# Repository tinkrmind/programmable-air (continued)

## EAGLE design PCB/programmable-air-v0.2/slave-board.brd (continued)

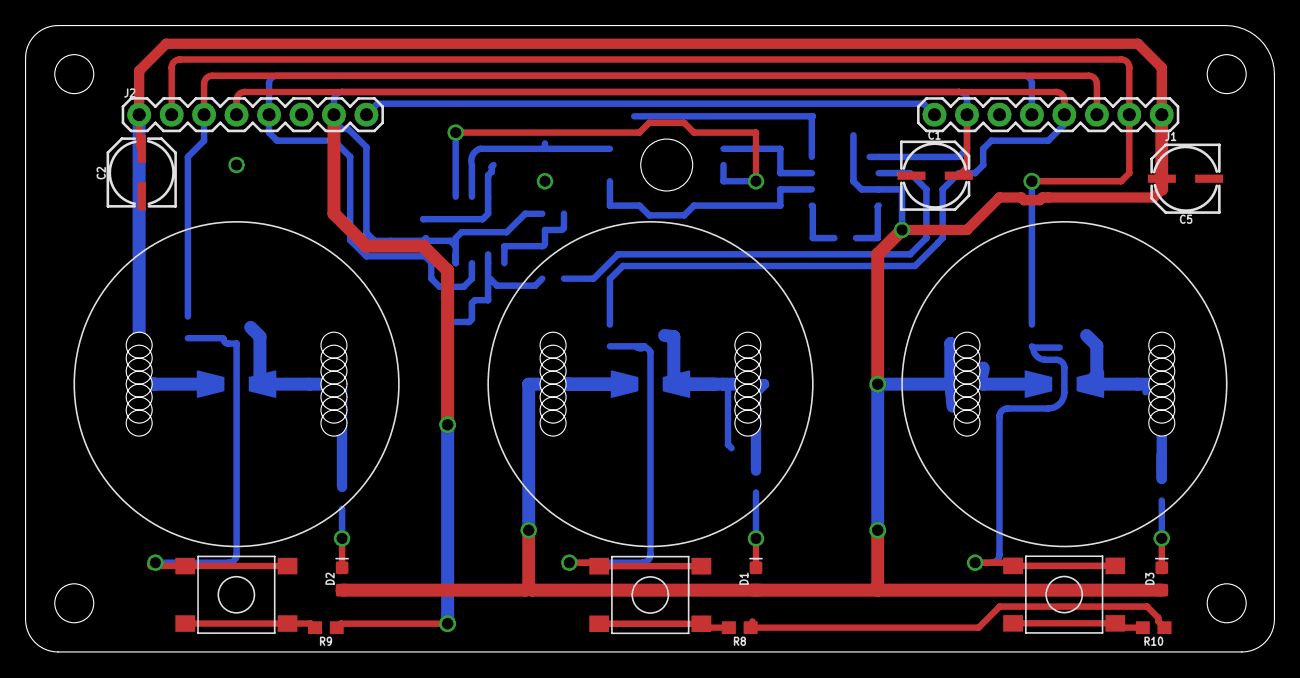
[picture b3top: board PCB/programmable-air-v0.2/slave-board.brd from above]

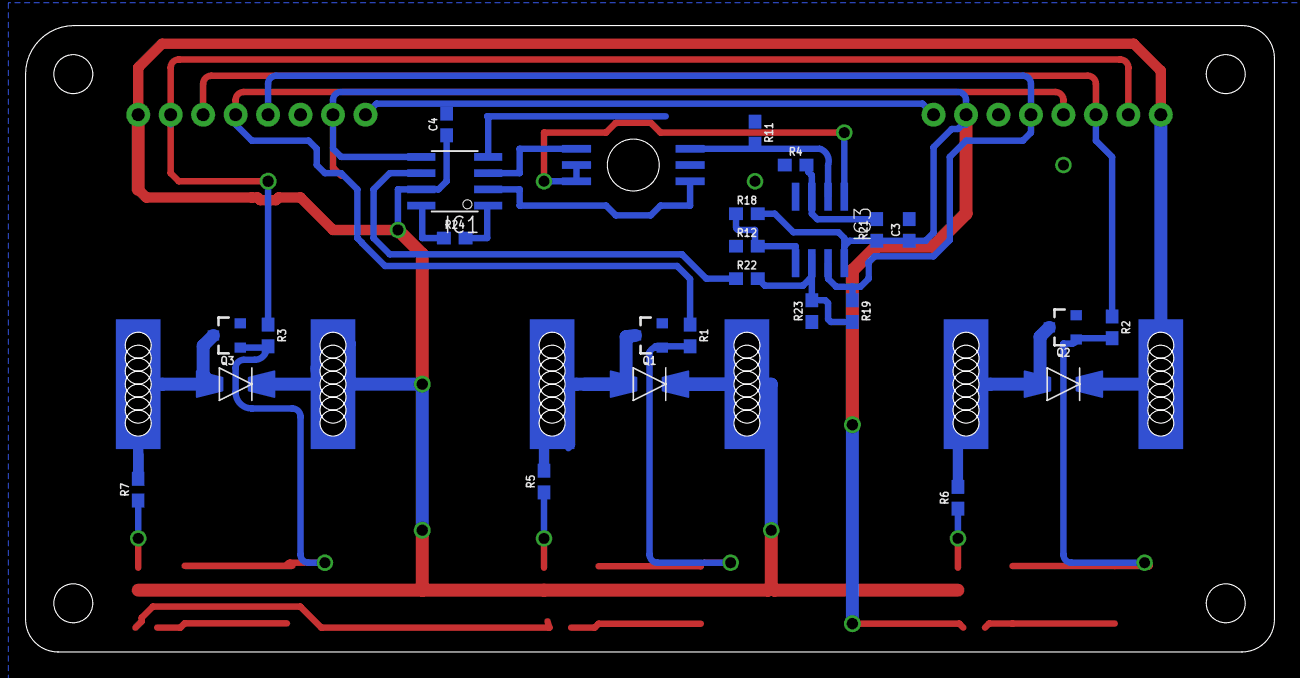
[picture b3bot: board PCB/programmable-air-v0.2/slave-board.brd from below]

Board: 2 copper layers, 97.7 x 49.0 mm, 43 parts (25 on the bottom side), 30 nets.

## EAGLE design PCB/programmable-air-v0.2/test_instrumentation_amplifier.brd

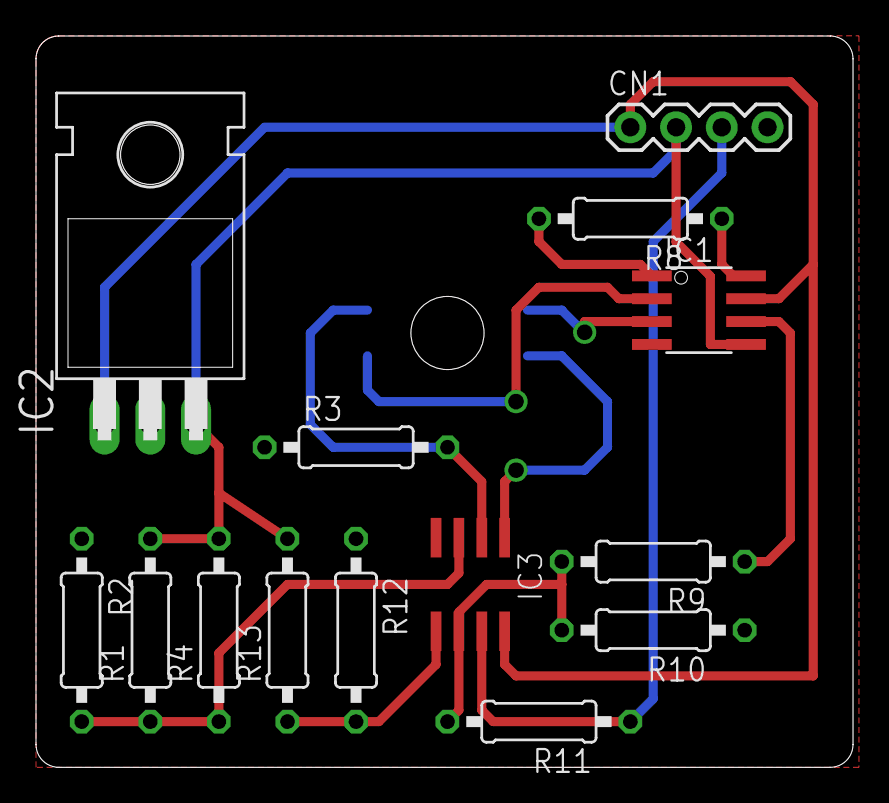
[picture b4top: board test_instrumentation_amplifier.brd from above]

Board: 2 copper layers, 45.4 x 40.6 mm, 15 parts (0 on the bottom side), 14 nets.

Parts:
CN1: 1X4-BIG; 1X04-BIG
IC1: INA126U; SO08
IC2: 7805T; TO220H
IC3: LM358MX; SO08
R1, R4: 30K; 0207/10
R2, R12, R13: 10K; 0207/10
R3: 20K; 0207/10
R8: 1.78K; 0207/10
R9, R10: 2K; 0207/10
R11: 1K; 0207/10
U$1: 2SMPP-03

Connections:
GND: CN1.4, IC1.4, IC2.2, IC3.4, R2.1, R3.1, R10.1, R12.1
unnamed: IC3.6, R9.2, R10.2, R11.2
unnamed: IC1.8, R8.1
unnamed: IC1.3, U$1.P$4
unnamed: CN1.2, IC1.5, IC2.3, R1.2, R4.2, R13.2
unnamed: IC1.1, R8.2
unnamed: IC1.2, U$1.P$1
unnamed: IC3.1, U$1.P$5, U$1.P$6
unnamed: IC1.6, R9.1
unnamed: IC3.3, R1.1, R2.2, R4.1
unnamed: IC3.5, R12.2, R13.1
unnamed: CN1.3, IC3.7, R11.1
unnamed: IC3.2, R3.2, U$1.P$3
VCC: CN1.1, IC1.7, IC2.1, IC3.8

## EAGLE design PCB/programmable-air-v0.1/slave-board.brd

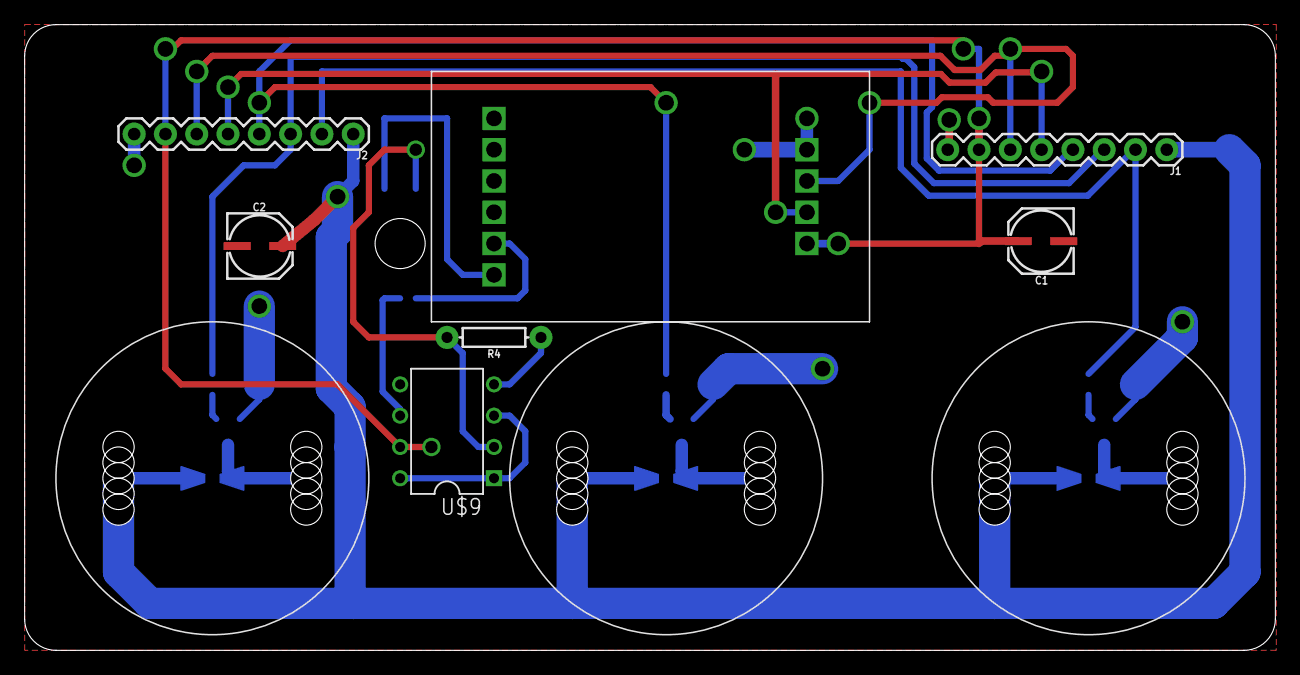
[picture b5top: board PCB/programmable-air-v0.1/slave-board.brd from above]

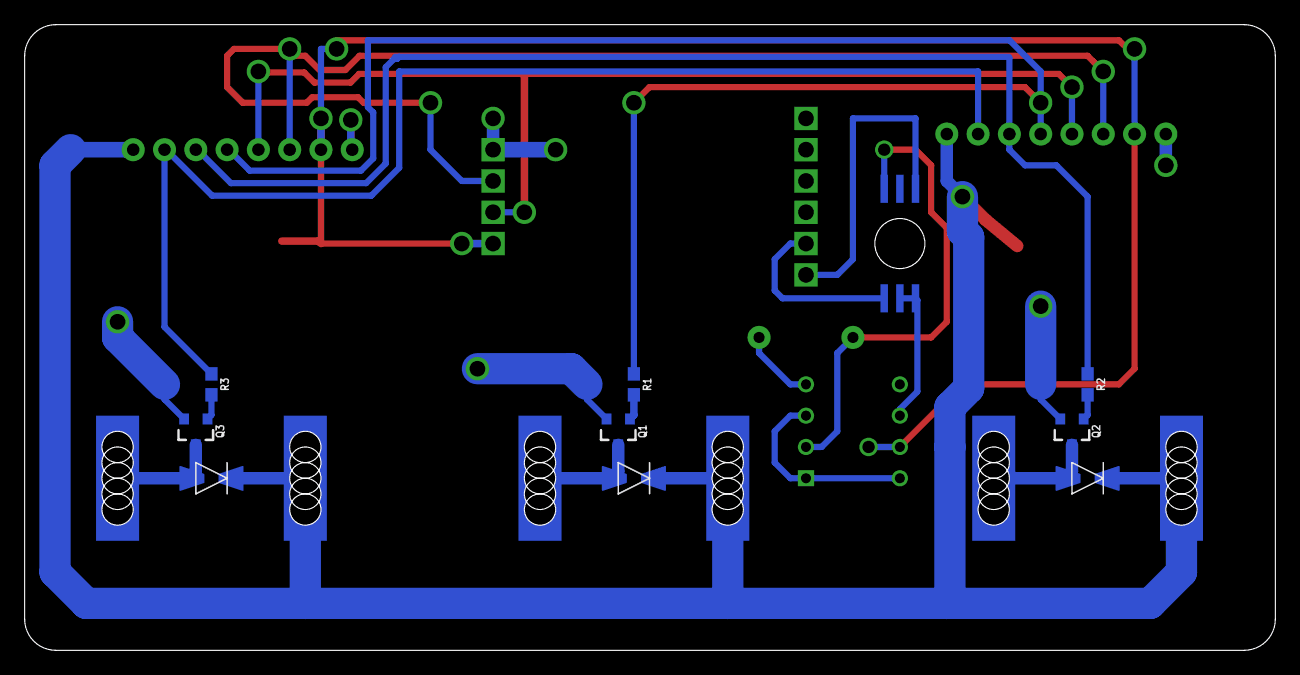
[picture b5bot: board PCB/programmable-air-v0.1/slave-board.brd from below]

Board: 2 copper layers, 101.5 x 50.8 mm, 20 parts (9 on the bottom side), 19 nets.

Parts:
C1, C2: 22uF; PANASONIC_C
J1, J2: 1X08
Q1, Q2, Q3: 600mA/40V; SOT23-3
R1, R2, R3: 1k; 0603
R4: AXIAL-0.3
U$1: HX711
U$2, U$3, U$4: CJV23-SOLENOID-VALVE; CJV23
U$5, U$6, U$7: IN4148
U$8: 2SMPP-03
U$9: LM10CN; DIP8

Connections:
GND: C1.-, C2.-, J1.8, J2.8, Q1.2, Q2.2, Q3.2, R4.P$1, U$1.P$7, U$9.4
unnamed: Q1.1, R1.2
unnamed: Q2.1, R2.2
unnamed: Q3.1, R3.2
unnamed: U$9.1, U$9.3, U$9.8
unnamed: J1.2, J2.2, R3.1
unnamed: Q3.3, U$4.P$2, U$7.P$2
unnamed: Q2.3, U$3.P$2, U$6.P$2
unnamed: Q1.3, U$2.P$2, U$5.P$2
unnamed: J1.3, J2.3, R2.1
unnamed: J1.4, J2.4, R1.1
unnamed: J1.5, J2.5, U$1.P$9
unnamed: J1.6, J2.6, U$1.P$8
unnamed: C1.+, J1.7, J2.7, U$1.P$10, U$9.7
unnamed: U$8.P$5, U$8.P$6, U$9.6
unnamed: R4.P$2, U$8.P$3, U$9.2
unnamed: U$1.P$6, U$8.P$1
unnamed: U$1.P$5, U$8.P$4
VIN: C2.+, J1.1, J2.1, U$2.P$1, U$3.P$1, U$4.P$1, U$5.P$1, U$6.P$1, U$7.P$1

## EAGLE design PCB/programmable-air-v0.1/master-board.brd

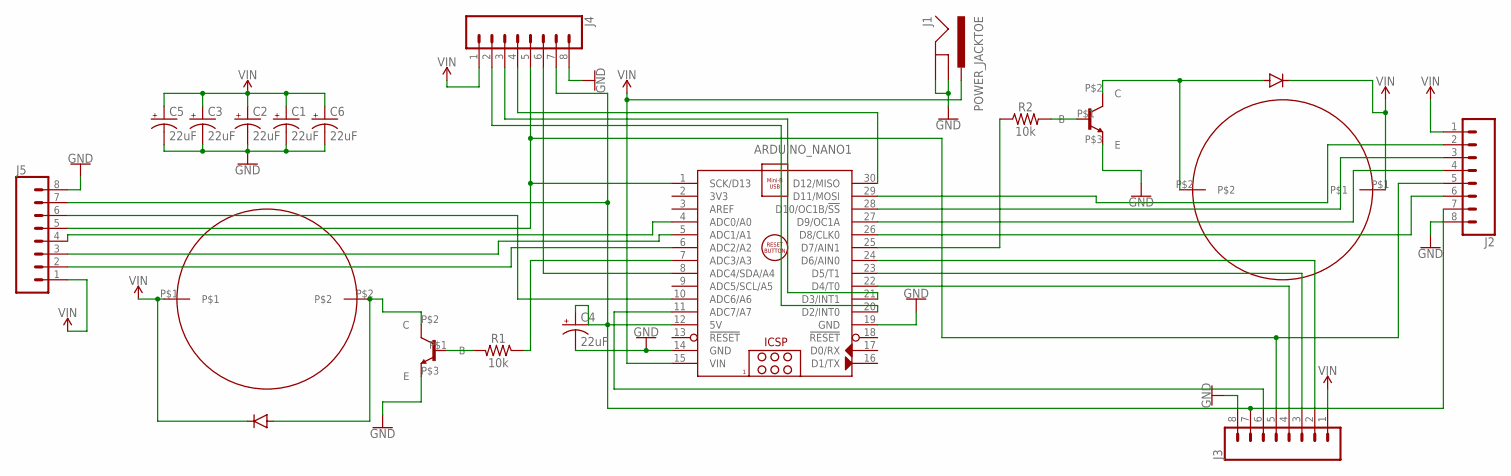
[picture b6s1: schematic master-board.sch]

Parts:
ARDUINO_NANO1: ARDUINO_NANO
C1, C2, C3, C4, C5, C6: 22uF; PANASONIC_C
J1: POWER_JACKTOE; POWER_JACK_SMD_OVERPASTE_TOE
J2, J3, J4, J5: CONN_08"; 1X08
R1, R2: 10k; 0603
U$1, U$2: AIYIMA-PUMP-A5F083; A5F083
U$3, U$4: IN4148
U$5, U$6: TIP120-TO220; TO220

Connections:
GND: ARDUINO_NANO1.14 (GND), ARDUINO_NANO1.19 (GND), C1.-, C2.-, C3.-, C4.-, C5.-, C6.-, J1.GND (GNDBREAK), J1.P$4 (GND), J2.8, J3.8, J4.8, J5.8, U$5.P$3 (E), U$6.P$3 (E)
unnamed: ARDUINO_NANO1.25 (D7/AIN1), R2.1
unnamed: R1.2, U$6.P$1 (B)
unnamed: ARDUINO_NANO1.22 (D4/T0), J3.4
unnamed: ARDUINO_NANO1.23 (D5/T1), J3.3
unnamed: U$1.P$2, U$3.P$2, U$6.P$2 (C)
unnamed: U$2.P$2, U$4.P$2, U$5.P$2 (C)
unnamed: R2.2, U$5.P$1 (B)
unnamed: ARDUINO_NANO1.21 (D3/INT1), J4.3
unnamed: ARDUINO_NANO1.24 (D6/AIN0), J3.2
unnamed: ARDUINO_NANO1.7 (ADC3/A3), R1.1
unnamed: ARDUINO_NANO1.8 (ADC4/SDA/A4), J4.6
unnamed: ARDUINO_NANO1.1 (SCK/D13), J2.5, J3.5, J4.5, J5.5
unnamed: ARDUINO_NANO1.10 (ADC6/A6), J5.6
unnamed: ARDUINO_NANO1.11 (ADC7/A7), J3.6
unnamed: ARDUINO_NANO1.20 (D2/INT0), J4.2
unnamed: ARDUINO_NANO1.30 (D12/MISO), J4.4
unnamed: ARDUINO_NANO1.12 (5V), C4.+, J2.7, J3.7, J4.7, J5.7
unnamed: ARDUINO_NANO1.26 (D8/CLK0), J2.6
unnamed: ARDUINO_NANO1.27 (D9/OC1A), J2.4
unnamed: ARDUINO_NANO1.28 (D10/OC1B/!SS), J2.3
unnamed: ARDUINO_NANO1.29 (D11/MOSI), J2.2
unnamed: ARDUINO_NANO1.6 (ADC2/A2), J5.2
unnamed: ARDUINO_NANO1.5 (ADC1/A1), J5.3
unnamed: ARDUINO_NANO1.4 (ADC0/A0), J5.4
VIN: ARDUINO_NANO1.15 (VIN), C1.+, C2.+, C3.+, C5.+, C6.+, J1.VIN0 (PWR), J2.1, J3.1, J4.1, J5.1, U$1.P$1, U$2.P$1, U$3.P$1, U$4.P$1

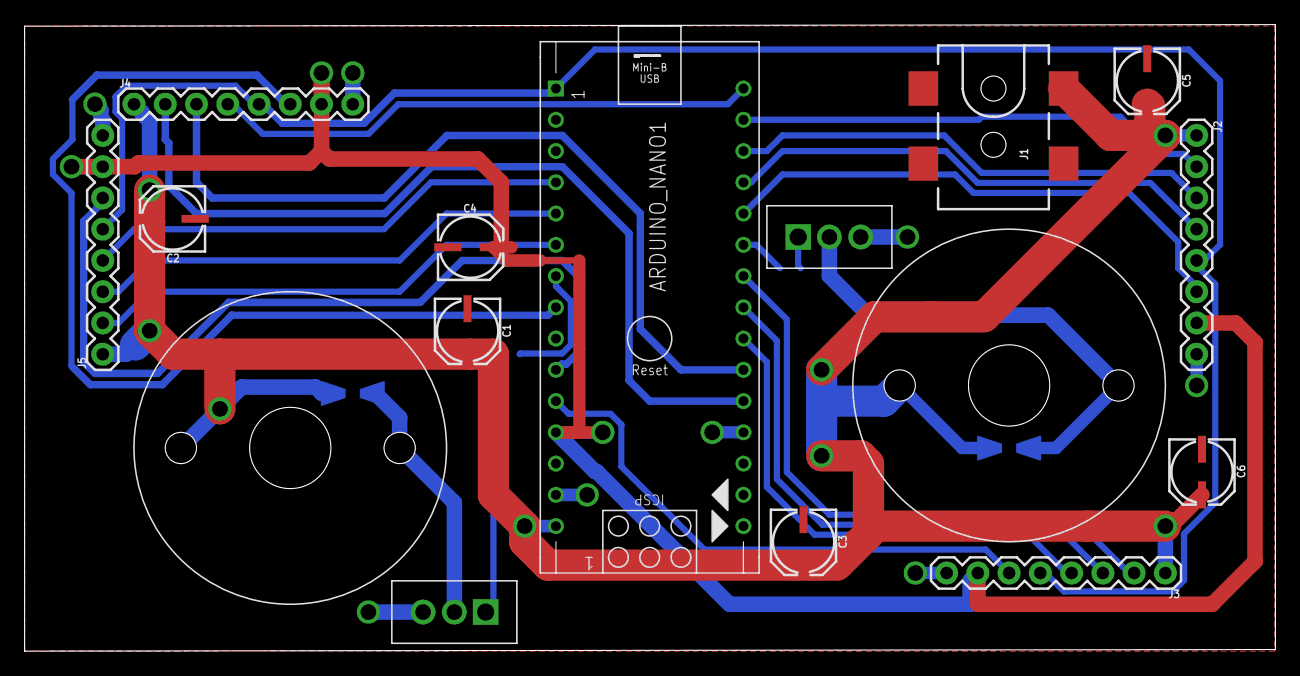
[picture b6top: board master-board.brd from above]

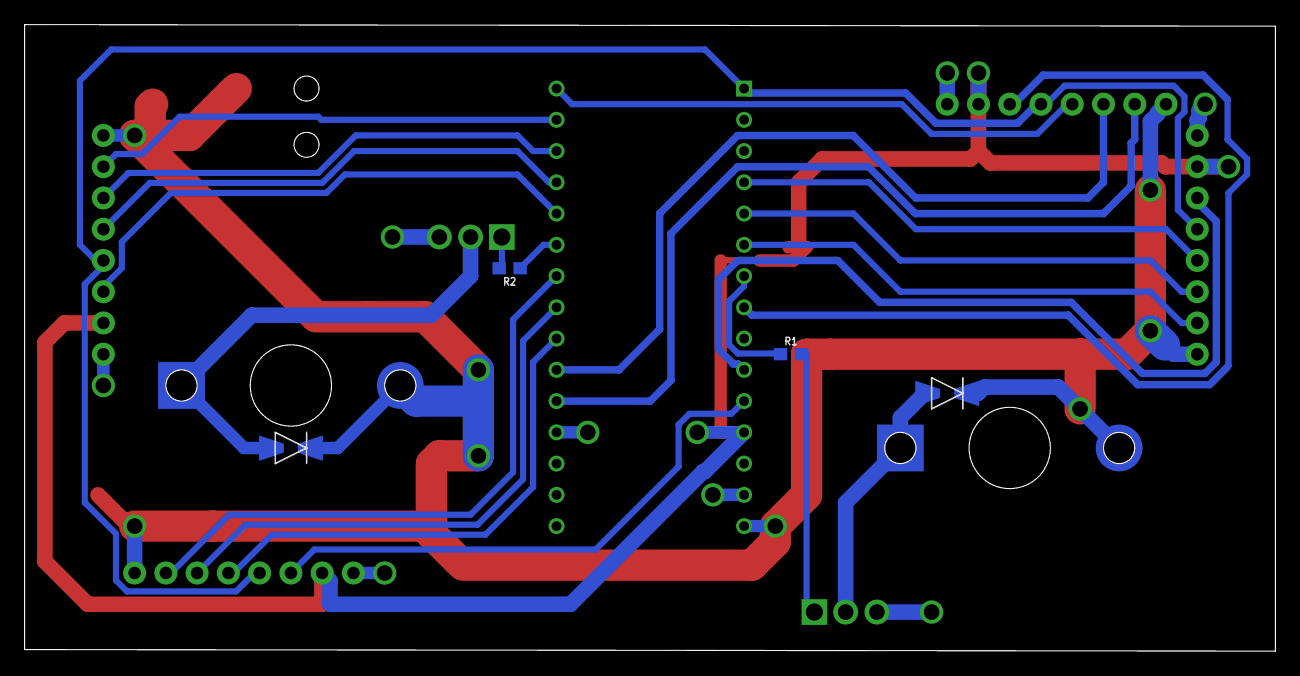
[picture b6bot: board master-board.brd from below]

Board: 2 copper layers, 101.7 x 50.9 mm, 20 parts (4 on the bottom side), 26 nets.

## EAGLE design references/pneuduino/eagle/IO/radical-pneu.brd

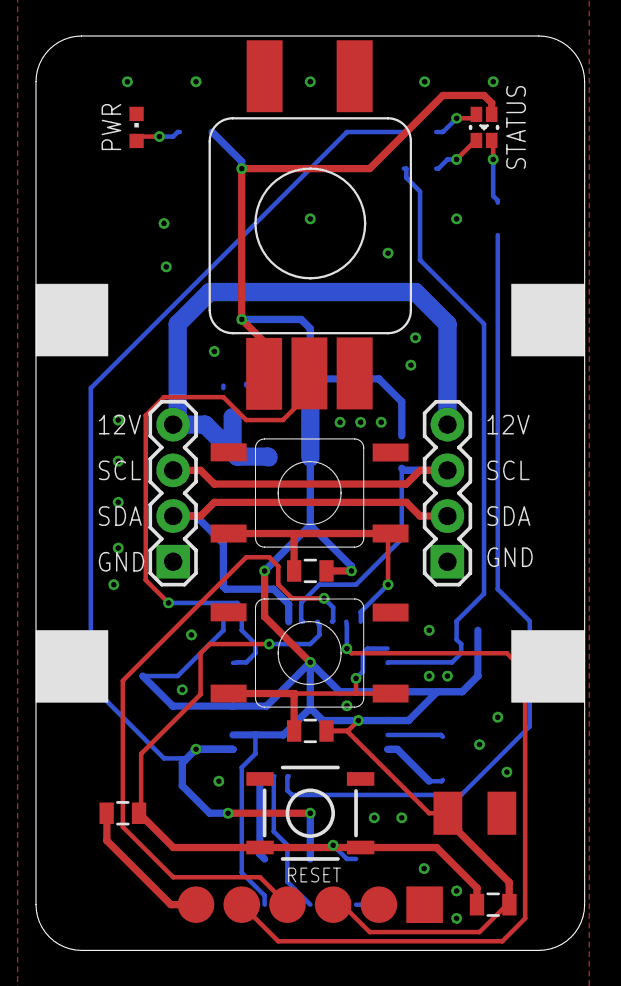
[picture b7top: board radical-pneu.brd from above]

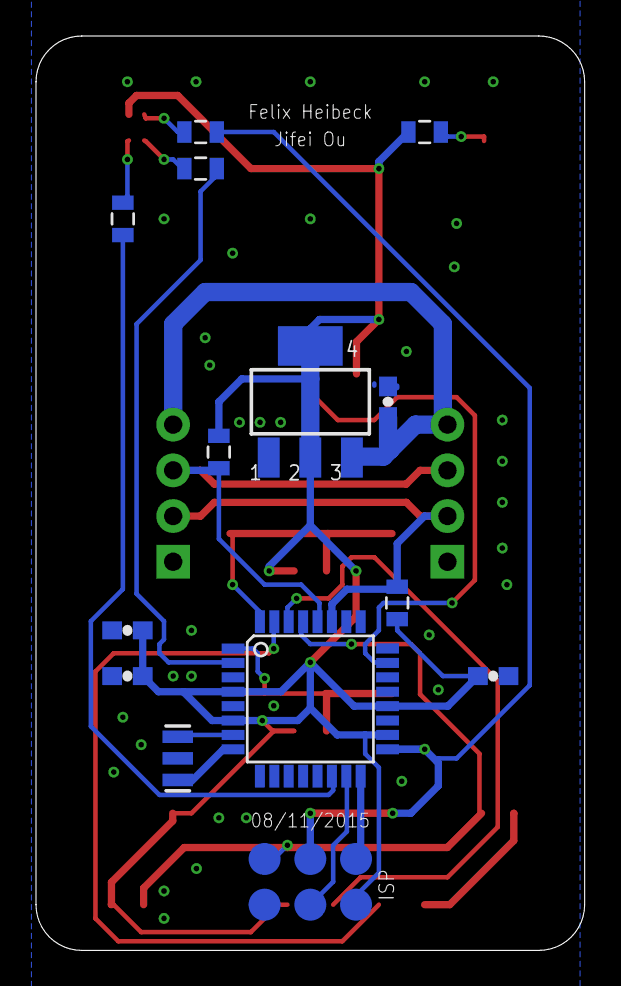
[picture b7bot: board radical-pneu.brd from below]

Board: 2 copper layers, 30.5 x 50.8 mm, 28 parts (14 on the bottom side), 23 nets.

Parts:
C1, C2, C8, C10: 0.1uF; 0603-CAP
C3: 22uF; SMC_B
C5: 0.1uF; 0805
IC3: ATMEGA328; TQFP32-08
JP2, JP3: 1X04
PWR: CHIPLED_0603
Q1: 16Mhz; RESONATOR-SMD
R1, R2, R3: 10K; 0805
R5, R6: 4.7k; 0805
R9, R11, R12, R13: 1k; 0805
S1: TAC_SWITCHSMD; TACTILE-SWITCH-SMD
U2: NCP1117-5; LINEAR_SOT223
U$1, U$3: RS-014R05; SWITCH-11MM
U$2: PRS11S
U$10: ISP_POGO; POGO_ISP
U$12: FTDI_POGO
U$21: LTST-C19FD1WT; LTST

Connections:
+5V: C2.1, C3.+, C8.1, C10.1, IC3.4, IC3.6, IC3.18, IC3.20, R1.1, R2.1, R3.1, R5.1, R6.2, R11.2, U2.2, U2.4, U$2.1, U$10.2, U$12.4, U$21.+
A0/POT: IC3.23, U$2.2
D2/BTN: IC3.32, R1.2, U$1.A, U$1.H
D3/BTN: IC3.1, R2.2, U$3.A, U$3.H
D4: IC3.2, R9.2
D10: IC3.14, R12.2
DTR: C5.2, U$12.1
GND: C1.2, C2.2, C3.-, C8.2, C10.2, IC3.3, IC3.5, IC3.21, JP2.1, JP3.1, PWR.C, Q1.2, S1.1, S1.2, U2.1, U$1.B, U$1.D, U$2.3, U$3.B, U$3.D, U$10.6, U$12.5, U$12.6
MISO: IC3.16, U$10.1
MOSI: IC3.15, U$10.4
unnamed: IC3.8, Q1.1
unnamed: IC3.7, Q1.3
unnamed: PWR.A, R11.1
unnamed: R9.1, U$21.R
unnamed: R12.1, U$21.G
unnamed: R13.1, U$21.B
RESET: C5.1, IC3.29, R3.2, S1.3, S1.4, U$10.5
RX: IC3.30, U$12.3
SCK: IC3.17, R13.2, U$10.3
SCL: IC3.28, JP2.3, JP3.3, R6.1
SDA: IC3.27, JP2.2, JP3.2, R5.2
TX: IC3.31, U$12.2
VIN: C1.1, JP2.4, JP3.4, U2.3

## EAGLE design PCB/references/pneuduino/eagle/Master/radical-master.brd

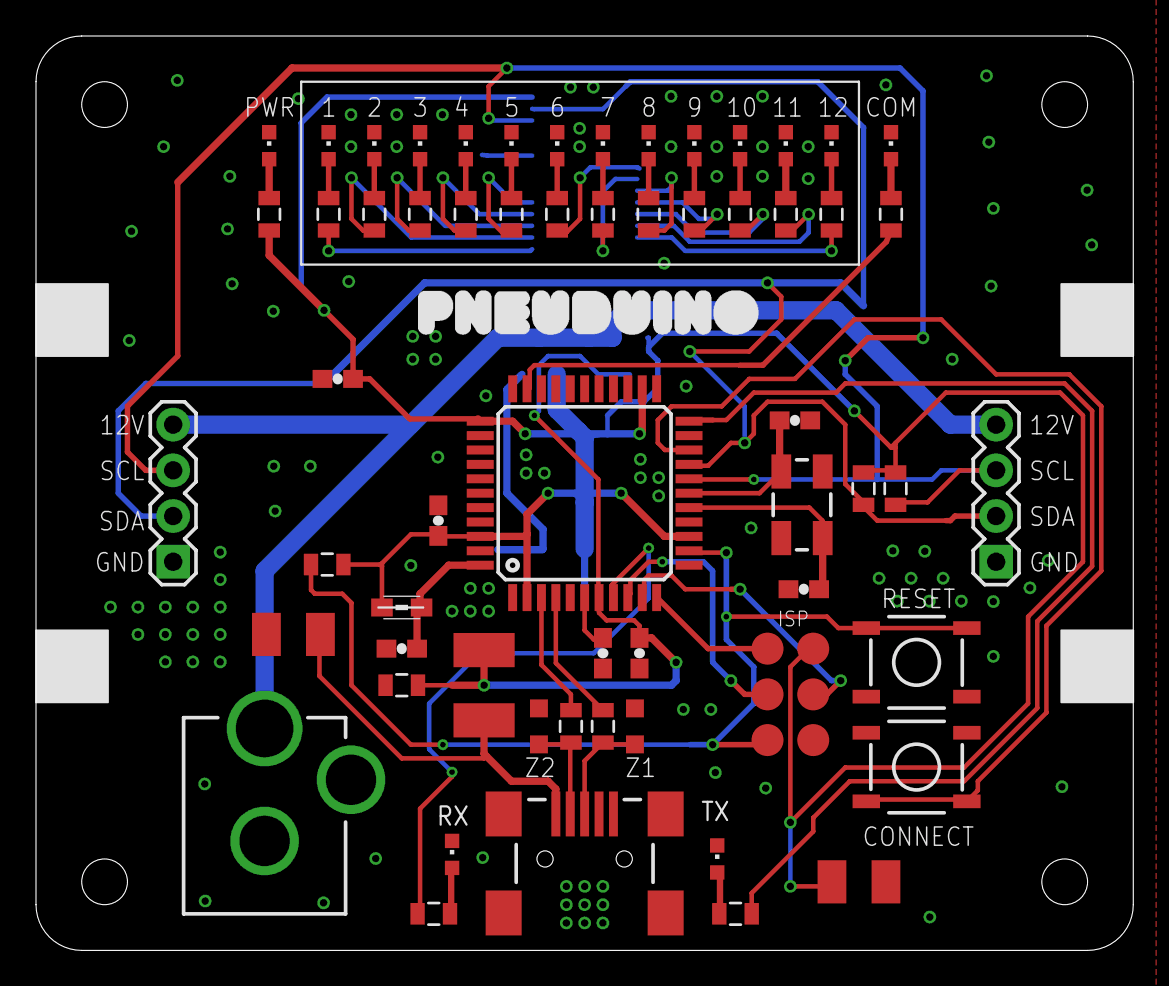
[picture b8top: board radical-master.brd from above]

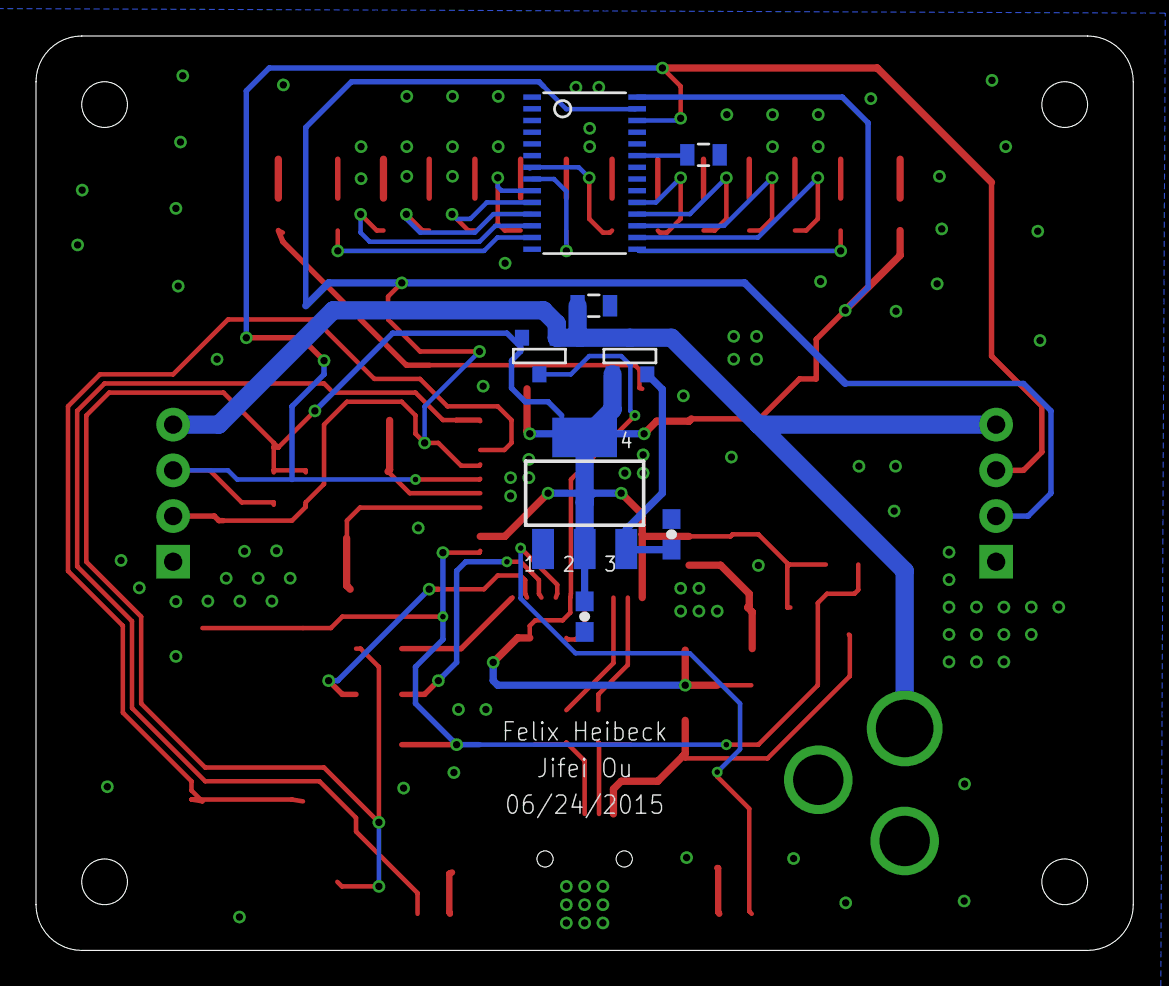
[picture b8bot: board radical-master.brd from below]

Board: 2 copper layers, 61.0 x 50.8 mm, 68 parts (8 on the bottom side), 53 nets.

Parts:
1, 2, 3, 4, 5, 6, 7, 8, 9, 10, 11, 12: CHIPLED_0603
C1, C2, C6, C8, C10: 0.1uF; 0603-CAP
C3, C14: 22uF; SMC_B
C4, C7: 1uF; 0603-CAP
C16, C17: 22pF; 0603-CAP
CN1: DCJACK_2MM_PTH
COM: CHIPLED_0603
F1: MF-MSMF050-2 500mA; L1812
JP1, JP2: 1X04
L1: MH2029-300Y; 0805
PWR: CHIPLED_0603
R1, R4: 22; 0805
R2, R3, R9, R12: 10K; 0805
R5, R6: opt; 0805
R10, R11, R13, R14, R15, R16, R17, R18, R19, R20, R21, R22, R23, R24, R25, R26: 1k; 0805
RX: CHIPLED_0603
S1, S2: TAC_SWITCHSMD; TACTILE-SWITCH-SMD
T1: FDN340P/PMV48XP; SOT-23
T2: PMV48XP; SOT-23
TX: CHIPLED_0603
U1: TSSOP28
U2: NCP1117-5; LINEAR_SOT223
U$3: USB-MINIB-5PIN; USB-MINIB
U$4: ATMEGA32U4-AU; TQFP44
U$10: ISP_POGO; POGO_ISP
Y2: 16MHz; CRYSTAL-SMD-5X3
Z1, Z2: CG0603MLC-05E; CT/CN0603

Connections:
+5V: C2.1, C3.+, C8.1, C10.1, L1.1, R3.1, R5.1, R6.2, R11.2, T1.2, T2.3, U1.28, U2.2, U2.4, U$4.2, U$4.14, U$4.24, U$4.34, U$4.42, U$10.2
+VIN: C1.1, T2.2, U2.3
BTN: S2.1, S2.2, U$4.20
D13: R10.2, U$4.32
D+: R4.1, U$3.D+, Z1.1
D-: R1.1, U$3.D-, Z2.1
GND: 1.C, 2.C, 3.C, 4.C, 5.C, 6.C, 7.C, 8.C, 9.C, 10.C, 11.C, 12.C, C1.2, C2.2, C3.-, C4.1, C6.2, C7.2, C8.2, C10.2, C14.-, C16.2, C17.2, CN1.GND, COM.C, JP1.1, JP2.1, PWR.C, R2.1, R9.1, R12.2, RX.C, S1.1, S1.2, S2.3, S2.4, TX.C, U1.1, U1.2, U1.3, U1.4, U1.5, U1.14, U1.24, U1.25, U2.1, U$3.GND, U$3.MTN1, U$3.MTN2, U$3.MTN3, U$3.MTN4, U$4.5, U$4.15, U$4.23, U$4.33, U$4.35, U$4.43, U$10.6, Z1.2, Z2.2
LED1: R13.2, U1.15
LED2: R14.2, U1.16
LED3: R15.2, U1.17
LED4: R16.2, U1.18
LED5: R17.2, U1.19
LED6: R18.2, U1.7
LED7: R19.2, U1.8
LED8: R20.2, U1.9
LED9: R21.2, U1.10
LED10: R22.2, U1.11
LED11: R25.2, U1.12
LED12: R26.2, U1.13
MISO: U$4.11, U$10.1
MOSI: U$4.10, U$10.4
unnamed: C16.1, U$4.17, Y2.3
unnamed: C17.1, U$4.16, Y2.1
unnamed: C7.1, U$4.6
unnamed: C4.2, L1.2, U$4.44
unnamed: R23.1, RX.A
unnamed: R24.1, TX.A
unnamed: COM.A, R10.1
unnamed: PWR.A, R11.1
unnamed: R12.1, U1.23
unnamed: 1.A, R13.1
unnamed: 2.A, R14.1
unnamed: 3.A, R15.1
unnamed: 4.A, R16.1
unnamed: 5.A, R17.1
unnamed: 6.A, R18.1
unnamed: 7.A, R19.1
unnamed: 8.A, R20.1
unnamed: 9.A, R21.1
unnamed: 10.A, R22.1
unnamed: 11.A, R25.1
unnamed: 12.A, R26.1
RD+: R4.2, U$4.4
RD-: R1.2, U$4.3
RESET: R3.2, S1.3, S1.4, U$4.13, U$10.5
RXLED: R23.2, U$4.8
SCK: U$4.9, U$10.3
SCL: JP1.3, JP2.3, R6.1, U1.26, U$4.18
SDA: JP1.2, JP2.2, R5.2, U1.27, U$4.19
TXLED: R24.2, U$4.22
VIN: CN1.PWR, JP1.4, JP2.4, R9.2, T1.3, T2.1
VUSB: C6.1, F1.2, R2.2, T1.1, U$4.7
VUSBD: C14.+, F1.1, U$3.VBUS

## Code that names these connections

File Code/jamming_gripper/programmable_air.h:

// Programmable Air
// Author: tinkrmind
// github.com/tinkrmind/programmable-air
// v0.3

#define DEBUG 0

#include <Adafruit_NeoPixel.h>

#define INCREASING 1
#define DECREASING -1
#define UN_KNOWN 0

const int pump[2] = {10, 11};
const int pump_sense[2] = {A6, A7};

#define OPEN 1
#define CLOSE 0
// vacuum, atmosphere, pressure
const int valve[9] = {   5,  4,  6,  \
                         8,  7,  9,  \
                         A1, A4, A0
                     };

const int sense[3] = {A3, A2, A5};

int readPressure(int num = 0, int times = 1);

#define neopixelPin 12
const int btn[2] = { 2, 3 };
const int btn1 = 2;
const int btn2 = 3;

Adafruit_NeoPixel neopixel = Adafruit_NeoPixel(3, neopixelPin, NEO_GRB + NEO_KHZ800);

void initializePins() {
  for (int i = 0; i < 9; i++) {
    pinMode(valve[i], OUTPUT);
    digitalWrite(valve[i], LOW);
  }

  pinMode(SCK, OUTPUT);

  pinMode(btn[0], INPUT_PULLUP);
  pinMode(btn[1], INPUT_PULLUP);

  for (int i = 0; i < 2; i++) {
    pinMode(pump[i], OUTPUT);
    digitalWrite(pump[i], LOW);
  }

  neopixel.begin();
  for (int i = 0; i < 3; i++) {
    neopixel.setPixelColor(i, neopixel.Color(1, 0, 1));
  }
  neopixel.show();
  if (DEBUG) {
    Serial.println("Pins initialised.");
  }
}

void setAllValves(int position) {
  if (position == OPEN) {
    for (int i = 0; i < 12; i++) {
      digitalWrite(valve[i], HIGH);
    }
  }

  if (position == CLOSE) {
    for (int i = 0; i < 12; i++) {
      digitalWrite(valve[i], LOW);
    }
  }
}

void setValve(int number, int position) {
  if (position == OPEN) {
    digitalWrite(valve[number], HIGH);
  }

  if (position == CLOSE) {
    digitalWrite(valve[number], LOW);
  }
}
//0-blow, 1-vent, 2-suck
void blow(int i) {
  if (DEBUG) {
    Serial.print("Blow: ");
    Serial.println(i);
  }
  if (i >= 0 && i <= 2) {
    setValve(i * 3 + 0, OPEN);
    setValve(i * 3 + 1, CLOSE);
    setValve(i * 3 + 2, CLOSE);
  }
}

void vent(int i) {
  if (DEBUG) {
    Serial.print("Vent: ");
    Serial.println(i);
  }
  if (i >= 0 && i <= 2) {
    setValve(i * 3 + 0, CLOSE);
    setValve(i * 3 + 1, OPEN);
    setValve(i * 3 + 2, CLOSE);
  }
}

void ventQuick(int i) {
  if (DEBUG) {
    Serial.print("ventQuick: ");
    Serial.println(i);
  }
  if (i >= 0 && i <= 2) {
    setValve(i * 3 + 0, CLOSE);
    setValve(i * 3 + 1, OPEN);
    setValve(i * 3 + 2, OPEN);
  }
}

void suck(int i) {
  if (DEBUG) {
    Serial.print("Suck: ");
    Serial.println(i);
  }
  if (i >= 0 && i <= 2) {
    setValve(i * 3 + 0, CLOSE);
    setValve(i * 3 + 1, CLOSE);
    setValve(i * 3 + 2, OPEN);
  }
}

void closeAll(int i) {
  if (DEBUG) {
    Serial.print("Close all: ");
    Serial.println(i);
  }
  if (i >= 1 && i <= 3) {
    i = i - 1;
    setValve(i * 3 + 0, CLOSE);
    setValve(i * 3 + 1, CLOSE);
    setValve(i * 3 + 2, CLOSE);
  }
}

// Read pressure
int readPressure(int num = 0, int times = 1) {
  //  Serial.print("reading pressure sensor ");
  //  Serial.print(num);
  //  Serial.print(" Averaging ");
  //  Serial.print(times);
  //  Serial.println(" times.");

  long pressure = 0;

  for (int i = 0; i < times; i++) {
    pressure += analogRead(sense[num]);
  }
  pressure /= times;

  //  Serial.print("Pressure: ");
  //  Serial.println(pressure);
  return int(pressure);
}

void switchOnPump(int num,  int percentagePower = 100) {
  if (num == 1 || num == 2) {
    analogWrite(pump[num - 1], percentagePower * 255 / 100);
  }
}

void switchOffPump(int num, int percentagePower = 100) {
  if (num == 1 || num == 2) {
    analogWrite(pump[num - 1], percentagePower * 255 / 100);
  }
}

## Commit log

2018-03-19 Slides complete
2018-03-26 Restructured folders
2018-03-26 Added quad chart
2018-03-27 Added images
2018-04-02 Minor README changes
2018-04-02 Restructure+image change
2018-04-06 Added product table
2018-04-07 Added photos
2018-04-14 Started work on PCB v0.1
2018-04-14 Rearranged folders. Added PCB eagle files.
2018-04-14 Made pump nad valve PCB library. PCB Mockup made. Added arduino nano footprint.
2018-04-14 master board v0.1 complete.
2018-04-14 Started work on slave PCB. Made changes to master pcb after testing
2018-04-15 Modified README
2018-04-15 PCB v0.11 master ready for production
2018-04-15 Forgot to add 5V input to slave boards
2018-04-15 Fixed errors found after production, assembly and testing
2018-04-15 Final tests done. Pump test functional. Workinf on slave board now.
2018-04-15 Slave PCB v0.1 complete
2018-04-15 Modified slave PCB v0.1 based on production and assembly
2018-04-15 asthetic changes to slave PCB
2018-04-17 After SMPP03 first test
    SMPP03 not working with hx711. Have to test it separately first. Made a test board for it. Added some vias to slave board. Added HX711 test code
2018-04-18 Tested CJV23 valves
    Made pick and place machine. Added IO board 1. Have to design IO board PCB next.
2018-04-18 Started IOBoard1 schematic
2018-04-18 Added pick and place video. Added future directions.
2018-04-18 minor changes to readme.
2018-04-19 Added universal jamming gripper CAD and video. Modified basic_pick_and_place code.
2018-04-20 Added balloon example code
2018-04-22 Create LICENSE
2018-04-23 Added balloon CAD and media
2018-04-26 Added vacuum+blow balloon CAD and code
2018-04-26 Modified HX711 code. FInal code functional.
2018-04-26 Modified slave board to have LM10CN
2018-04-27 Added PCB for testing SMPP with LM10 and HX711. Added gitignore.
2018-04-27 Added clearance for easier production
2018-04-28 Post Rube Goldberg. Working on PCB v0.2
2018-04-28 Master PCB v0.2 schematic and positioning complee. Going to start routing
2018-04-28 Master PCB v0.2 routing complete
2018-04-28 PCB v0.2 slave board ready
2018-04-28 PCB v0.2 cosmetic changes
2018-04-28 Minor fixes to slave PCB after assembly. Started work on test code for PCB v0.2
2018-04-29 Modified README to add progress updates
2018-05-02 Added balloon face media.
2018-05-05 Added many new examlpe codes. Programmable Air library
2018-05-05 Added pressure control code
2018-05-05 Added media
2018-05-07 more new test code.
2018-05-07 Added example code for lips don't lie
2018-05-07 Added diagrams, presentation notes, no major changes to tech
2018-05-14 cosmetic chnges to readme
2018-05-18 Added test circuit schematic for new amplifier of pressure sensor
2018-06-03 Working towards instrumentation amplifier instead of HX711
    MCP6001 was a huge mistake. 6V Vin max. Modifying circuit to LM358.
2018-06-03 LM358 test board ready
2018-06-05 LM358 slave board ready
2018-06-05 LM358 slave board final
2018-06-05 Master board + Slave board in single PCB ready.
2018-06-19 Minor changes to the PCB
2018-07-07 Sent PCBs for fabrication
2018-08-16 Sent for second production run. New Logo.
2018-08-16 Reordering
2018-08-16 Changed media size
2018-08-16 Added 3d models
2018-08-17 Much ado about 3d modelling
2018-08-22 Changed header
2018-08-22 Update long header
2018-08-26 After sending to elecrow for manufacturing. v0.3 complete. New Logo
